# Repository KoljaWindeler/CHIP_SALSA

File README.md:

please go to 
http://koljawindeler.github.io/CHIP_SALSA

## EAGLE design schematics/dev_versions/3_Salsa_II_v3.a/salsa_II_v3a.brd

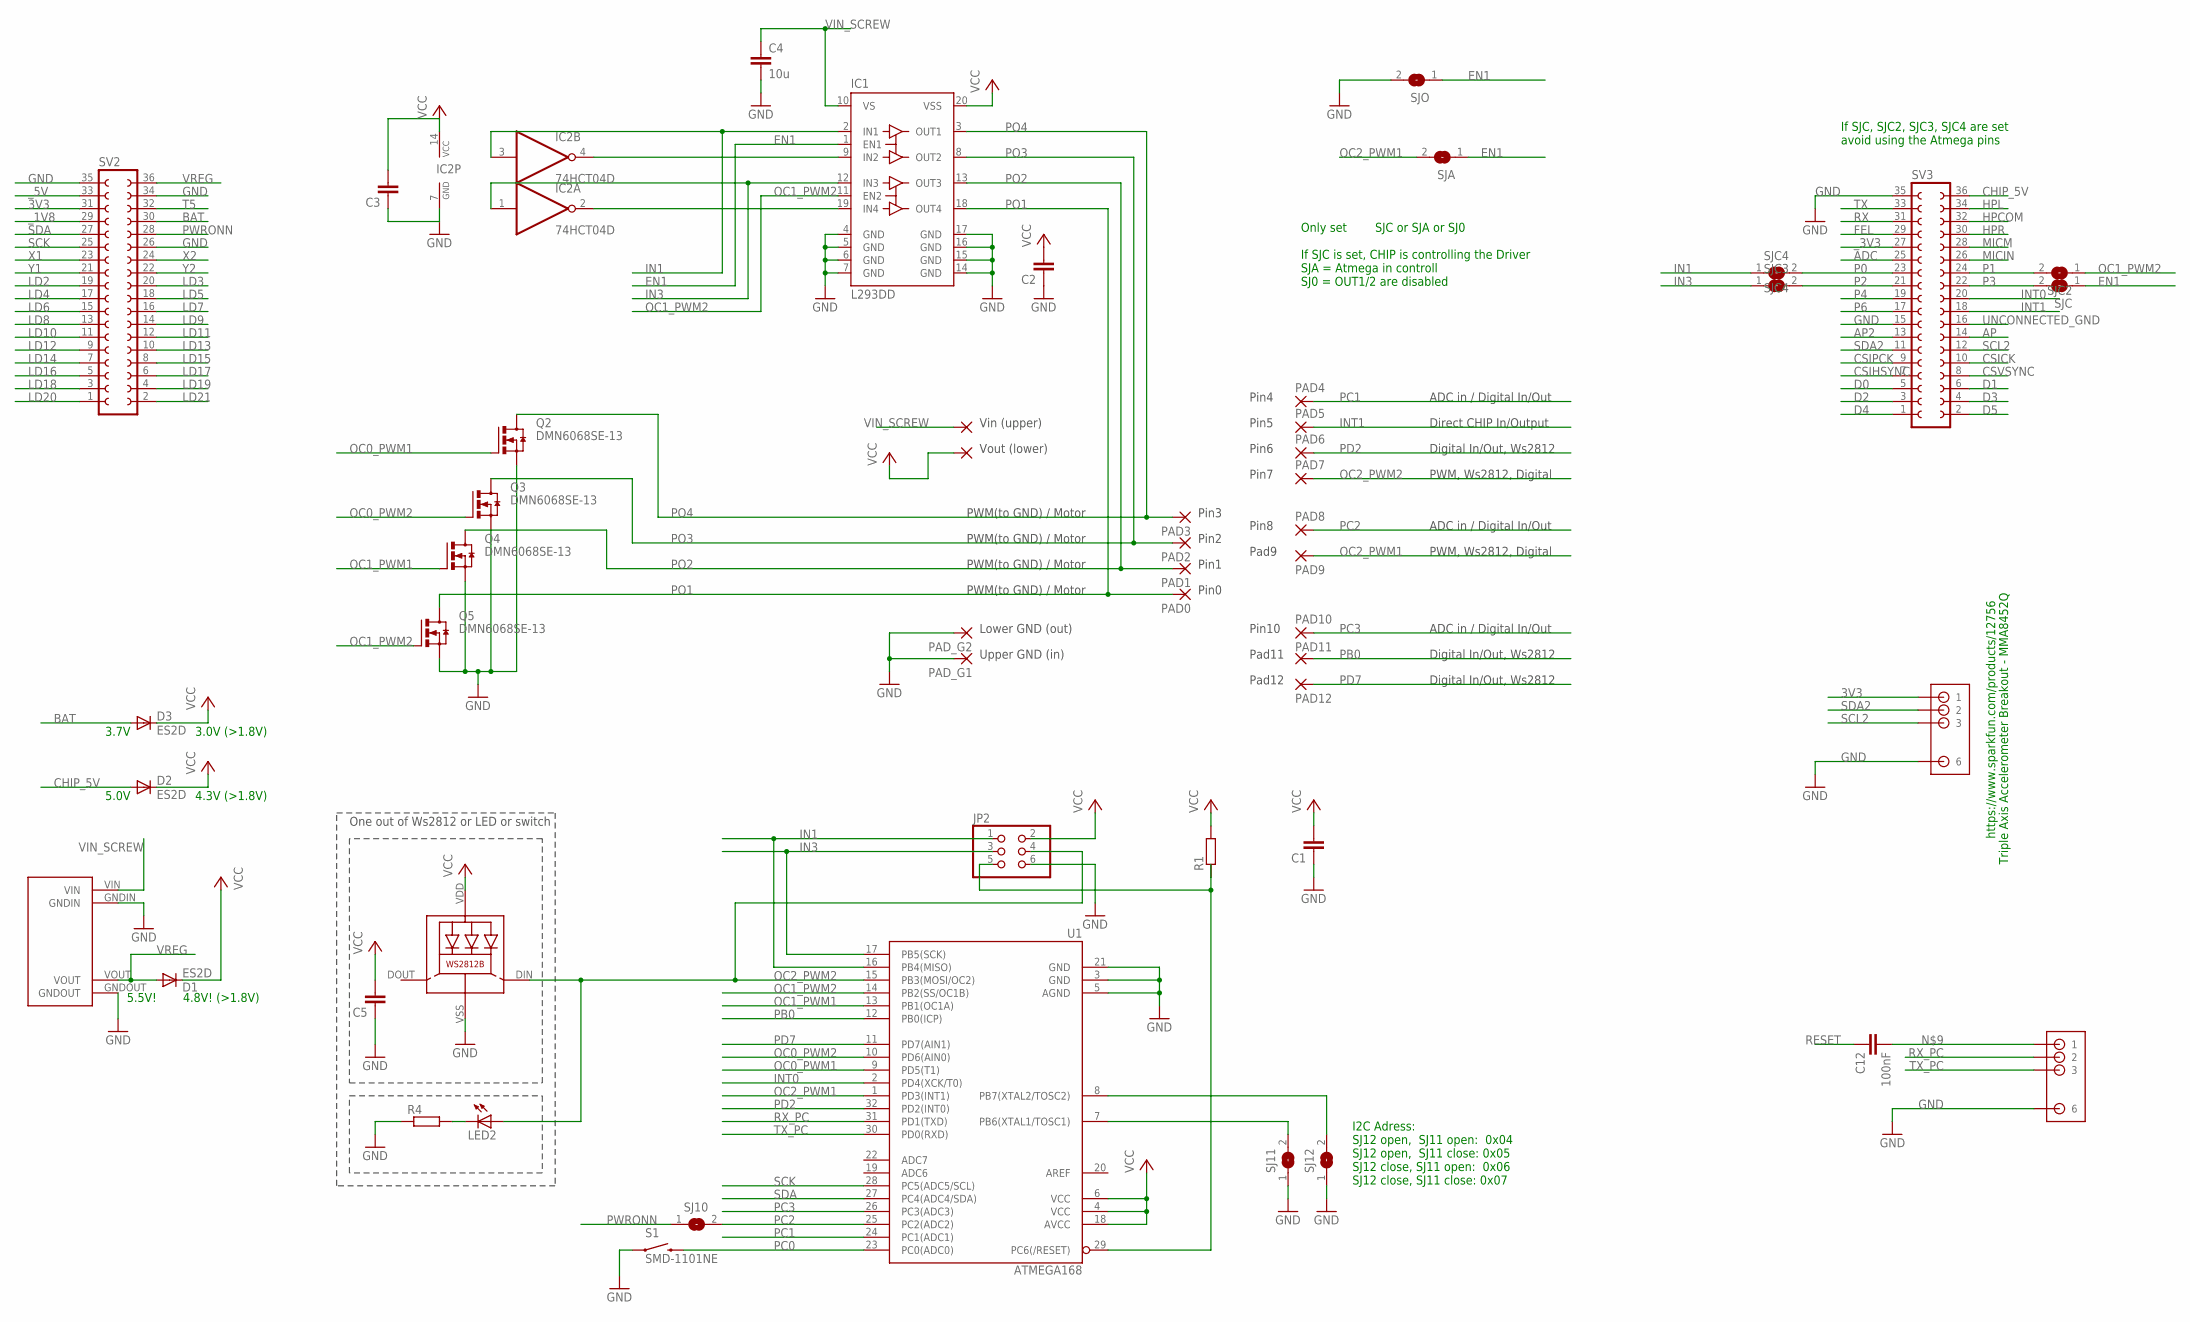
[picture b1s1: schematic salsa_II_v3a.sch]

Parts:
C1, C2, C3, C5: C-EUC0805; C0805
C4: 10u; C1210
C12: 100nF; C1206
D1, D2, D3: ES2D; SMB
IC1: L293DD; SO20
IC2: 74HCT04D; SO14
JP2: PINHD-2X3; 2X03
LED1: WS2812B
LED2: LEDCHIP-LED0805; CHIP-LED0805
PAD0, PAD1, PAD2, PAD3, PAD4, PAD5, PAD6, PAD7, PAD8, PAD10, PAD17: 3,17/1,3
PAD9, PAD12: SMD2; SMD1,27-2,54
PAD11: WIREPADSMD1,27-254; SMD1,27-2,54
PAD_G1, PAD_G2: 3,17/1,3
PAD_VIN: 3,17/1,3
Q2, Q3, Q4, Q5: DMN6068SE-13; SOT223
R1, R4: R-EU_M1206; M1206
S1: SMD-1101NE; TACTILE-SWITCH-1101NE
SJ10, SJ11, SJ12: SJ
SJA: SJ
SJC, SJC2, SJC3: SJ
SJC4: SJC4; SJ
SJO: SJ
SV2, SV3: FE18-2
U1: ATMEGA168; TQFP32-08
U$1: MP1584EN
U$3, U$4: 6_TO_4_HEADER

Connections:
3V3: SV2.31, U$4.1
ADC: SV3.25
AP: SV3.14
AP2: SV3.13
BAT: D3.A, SV2.30
CHIP_5V: D2.A, SV3.36
CSICK: SV3.10
CSIHSYNC: SV3.7
CSIPCK: SV3.9
CSVSYNC: SV3.8
D0: SV3.5
D1: SV3.6
D2: SV3.3
D3: SV3.4
D4: SV3.1
D5: SV3.2
EN1: IC1.1 (EN1), SJA.1, SJC.1, SJO.1
FEL: SV3.29
GND: C1.1, C2.1, C3.1, C4.2, C5.1, IC1.4 (GND), IC1.5 (GND), IC1.6 (GND), IC1.7 (GND), IC1.14 (GND), IC1.15 (GND), IC1.16 (GND), IC1.17 (GND), IC2.7 (GND), JP2.6, LED1.VSS (GND), PAD_G1.1, PAD_G2.1, Q2.3 (S), Q3.3 (S), Q4.3 (S), Q5.3 (S), R4.1, S1.P$1 (1), SJ11.1, SJ12.1, SJO.2, SV2.26, SV2.34, SV2.35, SV3.15, SV3.35, U1.3 (GND), U1.5 (AGND), U1.21 (GND), U$1.GNDIN, U$1.GNDOUT, U$3.6, U$4.6
HPCOM: SV3.32
HPL: SV3.34
HPR: SV3.30
IN1: IC1.2 (IN1), IC2.3 (I), JP2.1, SJC4.1, U1.16 (PB4(MISO))
IN3: IC1.12 (IN3), IC2.1 (I), JP2.3, SJC3.1, U1.17 (PB5(SCK))
INT0: SV3.20, U1.2 (PD4(XCK/T0))
INT1: PAD5.1, SV3.18
LD2: SV2.19
LD3: SV2.20
LD4: SV2.17
LD5: SV2.18
LD6: SV2.15
LD7: SV2.16
LD8: SV2.13
LD9: SV2.14
LD10: SV2.11
LD11: SV2.12
LD12: SV2.9
LD13: SV2.10
LD14: SV2.7
LD15: SV2.8
LD16: SV2.5
LD17: SV2.6
LD18: SV2.3
LD19: SV2.4
LD20: SV2.1
LD21: SV2.2
MICIN: SV3.26
MICM: SV3.28
unnamed: IC1.19 (IN4), IC2.2 (O)
unnamed: SJ11.2, U1.7 (PB6(XTAL1/TOSC1))
unnamed: SJ12.2, U1.8 (PB7(XTAL2/TOSC2))
unnamed: LED2.C, R4.2
unnamed: C12.2, U$3.1
unnamed: IC1.9 (IN2), IC2.4 (O)
OC0_PWM1: Q2.1 (G), U1.9 (PD5(T1))
OC0_PWM2: Q3.1 (G), U1.10 (PD6(AIN0))
OC1_PWM1: Q4.1 (G), U1.13 (PB1(OC1A))
OC1_PWM2: IC1.11 (EN2), Q5.1 (G), SJC2.1, U1.14 (PB2(SS/OC1B))
OC2_PWM1: PAD9.1, SJA.2, U1.1 (PD3(INT1))
OC2_PWM2: JP2.4, LED1.DIN (DI), LED2.A, PAD7.1, U1.15 (PB3(MOSI/OC2))
P0: SJC4.2, SV3.23
P1: SJC2.2, SV3.24
P2: SJC3.2, SV3.21
P3: SJC.2, SV3.22
P4: SV3.19
P6: SV3.17
PB0: PAD11.1, U1.12 (PB0(ICP))
PC0: S1.P$2 (2), U1.23 (PC0(ADC0))
PC1: PAD4.1, U1.24 (PC1(ADC1))
PC2: PAD8.1, SJ10.2, U1.25 (PC2(ADC2))
PC3: PAD10.1, U1.26 (PC3(ADC3))
PD2: PAD6.1, U1.32 (PD2(INT0))
PD7: PAD12.1, U1.11 (PD7(AIN1))
PO1: IC1.18 (OUT4), PAD0.1, Q5.2 (D), Q5.4 (D)
PO2: IC1.13 (OUT3), PAD1.1, Q4.2 (D), Q4.4 (D)
PO3: IC1.8 (OUT2), PAD2.1, Q3.2 (D), Q3.4 (D)
PO4: IC1.3 (OUT1), PAD3.1, Q2.2 (D), Q2.4 (D)
PWRONN: SJ10.1, SV2.28
RESET: C12.1, JP2.5, R1.1, U1.29 (PC6(/RESET))
RX: SV3.31
RX_PC: U1.31 (PD1(TXD)), U$3.2
SCK: SV2.25, U1.28 (PC5(ADC5/SCL))
SCL2: SV3.12, U$4.3
SDA: SV2.27, U1.27 (PC4(ADC4/SDA))
SDA2: SV3.11, U$4.2
T5: SV2.32
TX: SV3.33
TX_PC: U1.30 (PD0(RXD)), U$3.3
UNCONNECTED_GND: SV3.16
VCC: C1.2, C2.2, C3.2, C5.2, D1.C, D2.C, D3.C, IC1.20 (VSS), IC2.14 (VCC), JP2.2, LED1.VDD, PAD17.1, R1.2, U1.4 (VCC), U1.6 (VCC), U1.18 (AVCC)
VIN_SCREW: C4.1, IC1.10 (VS), PAD_VIN.1, U$1.VIN
VREG: D1.A, SV2.36, U$1.VOUT
X1: SV2.23
X2: SV2.24
Y1: SV2.21
Y2: SV2.22
_1V8: SV2.29
_3V3: SV3.27
_5V: SV2.33

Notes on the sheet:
https://www.sparkfun.com/products/12756
Triple Axis Accelerometer Breakout - MMA8452Q
Vin (upper)
Pin0
Pin1
Pin2
Pin3
Upper GND (in)
Lower GND (out)
Vout (lower)
Pin4
Pin5
Pad11
Pad12
Pad9
Pin6
Pin7
Pin8
Pin10
PWM(to GND) / Motor
ADC in / Digital In/Out
Direct CHIP In/Output
Digital In/Out, Ws2812
PWM, Ws2812, Digital
I2C Adress: SJ12 open, SJ11 open: 0x04 SJ12 open, SJ11 close: 0x05 SJ12 close, SJ11 open: 0x06 SJ12 close, SJ11 close: 0x07
Only set SJC or SJA or SJ0 If SJC is set, CHIP is controlling the Driver SJA = Atmega in controll SJ0 = OUT1/2 are disabled
If SJC, SJC2, SJC3, SJC4 are set avoid using the Atmega pins
One out of Ws2812 or LED or switch
5.5V!
4.8V! (>1.8V)
5.0V
4.3V (>1.8V)
3.0V (>1.8V)
3.7V

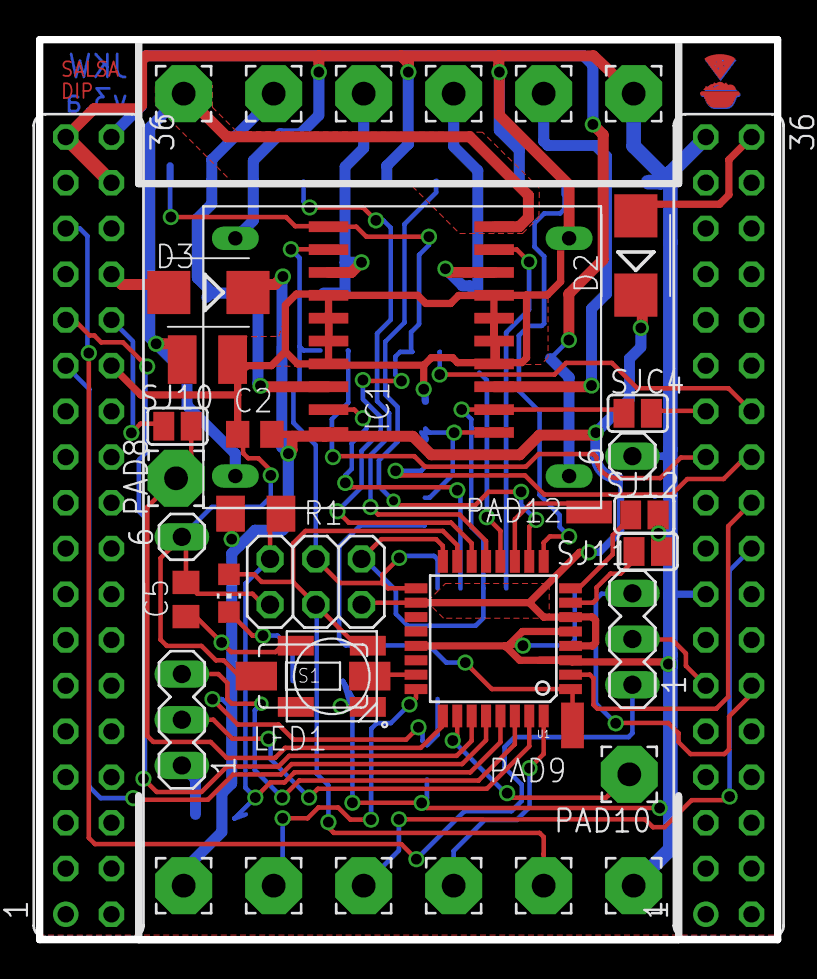
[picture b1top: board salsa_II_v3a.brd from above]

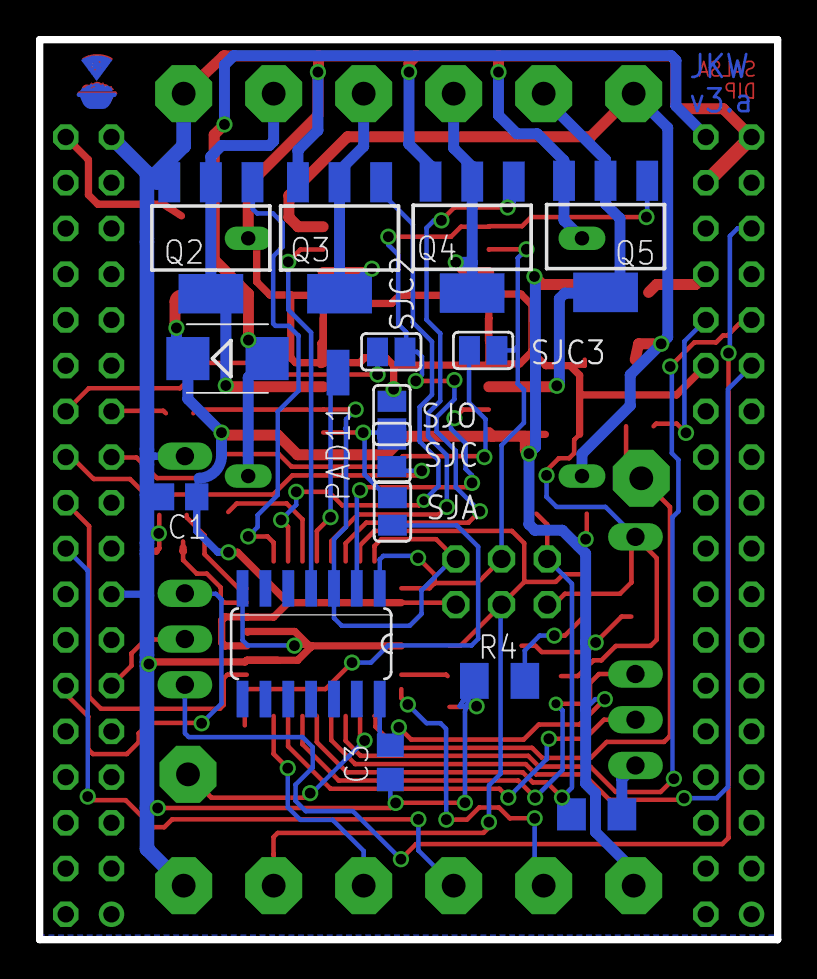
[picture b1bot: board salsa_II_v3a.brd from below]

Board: 2 copper layers, 41.0 x 50.0 mm, 55 parts (17 on the bottom side), 47 nets.

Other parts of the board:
U$2, U$5: LOGO

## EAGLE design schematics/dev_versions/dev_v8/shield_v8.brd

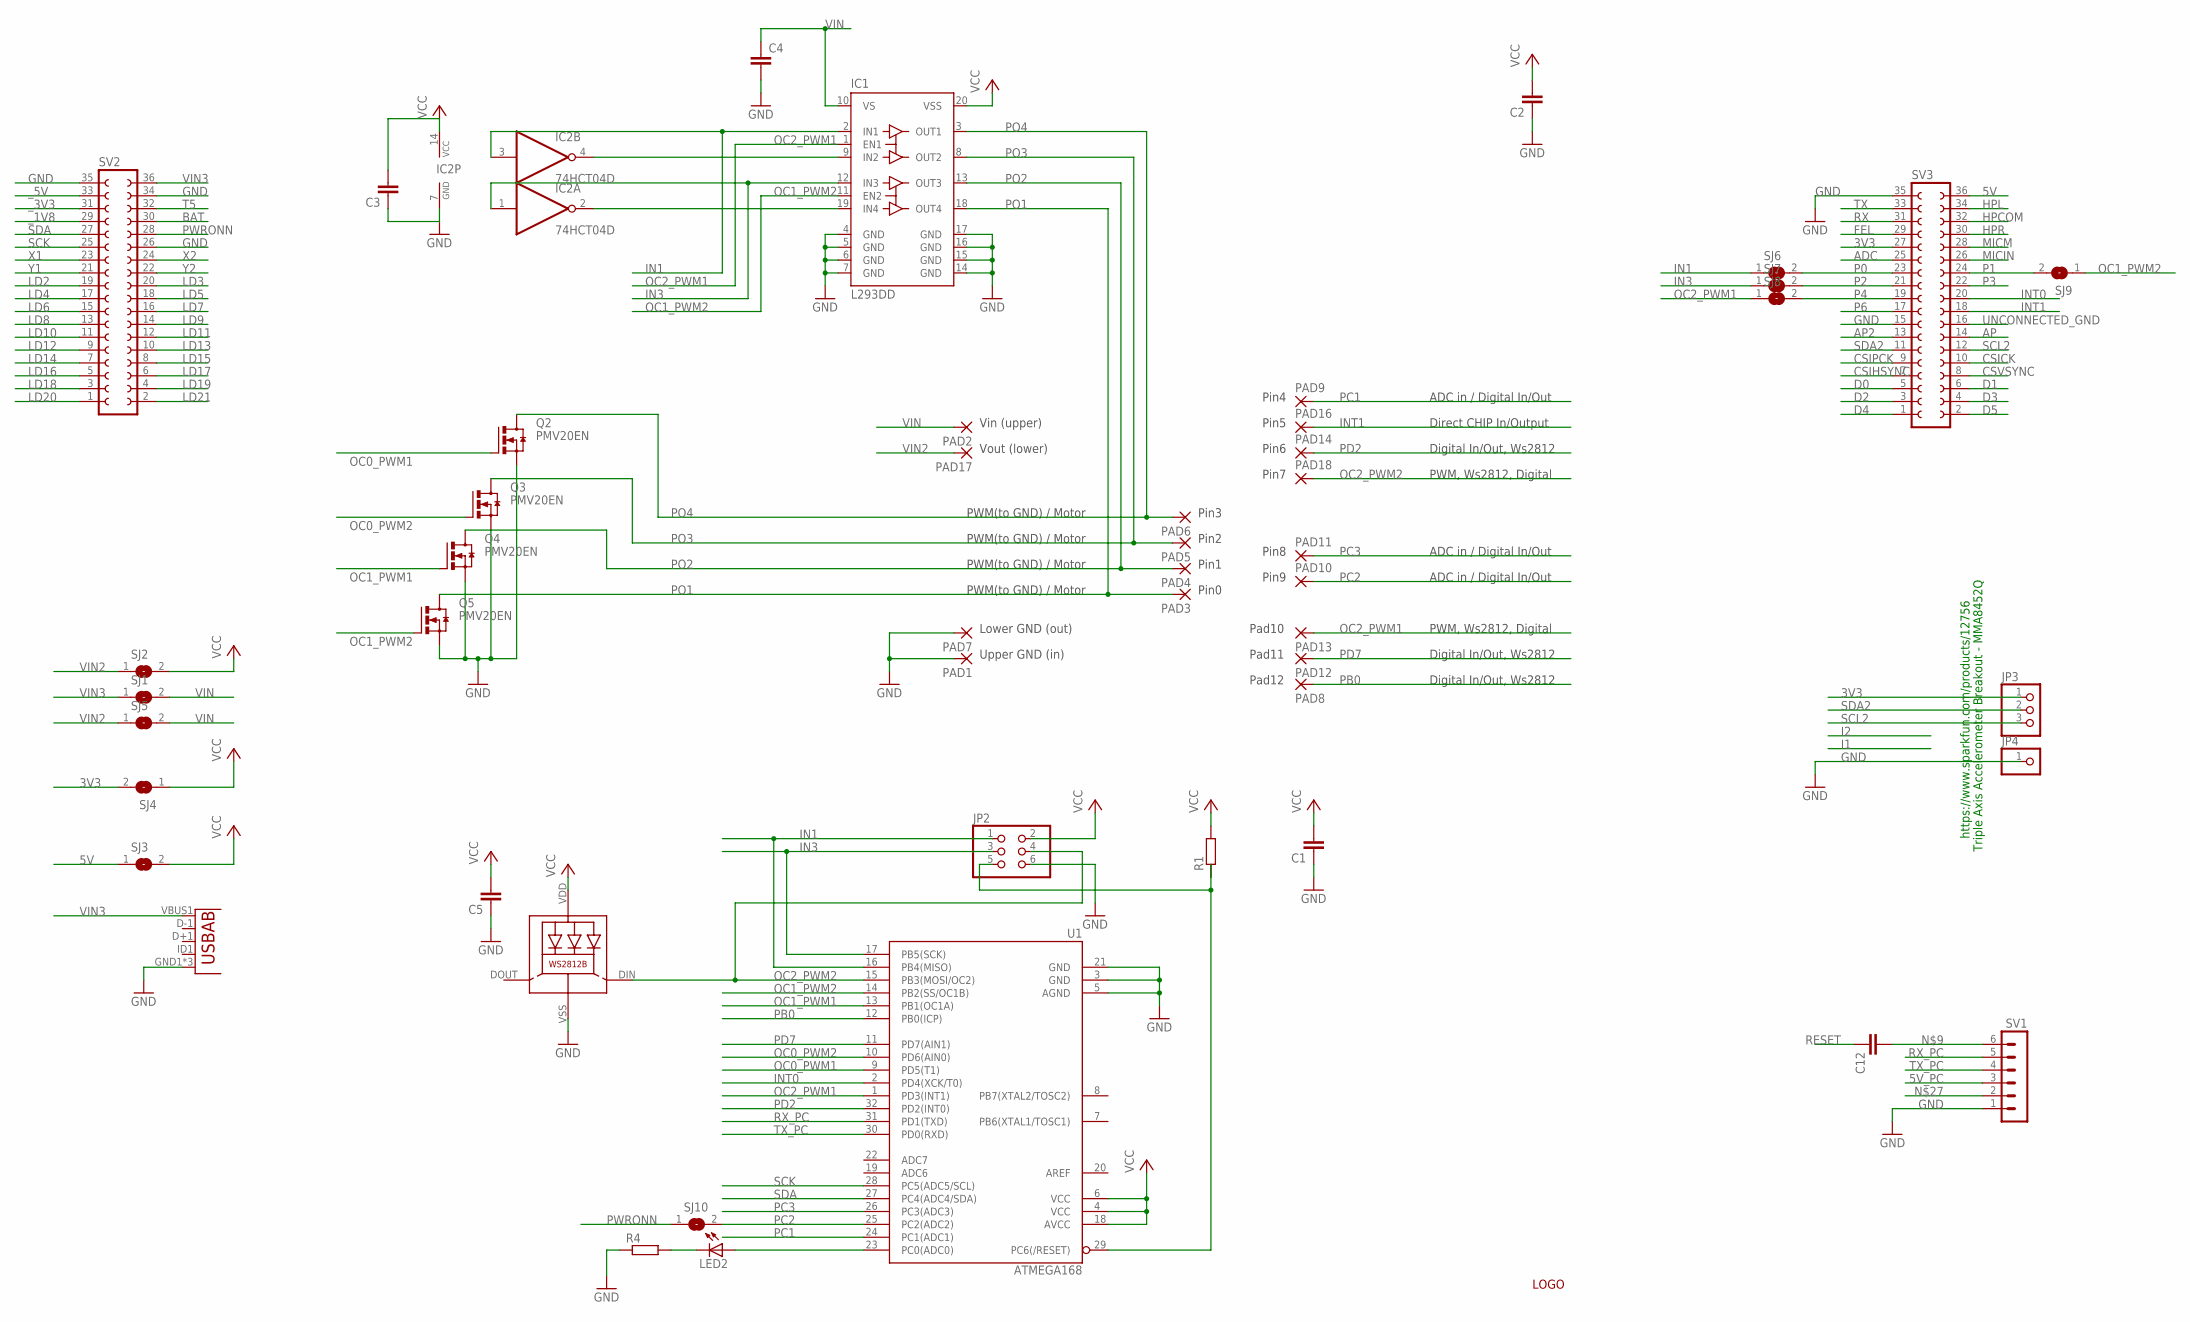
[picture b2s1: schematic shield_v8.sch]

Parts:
C1, C2, C3, C5: C-EUC0805; C0805
C4: C-EUC1210; C1210
C12: C-EUC1206; C1206
IC1: L293DD; SO20
IC2: 74HCT04D; SO14
JP2: PINHD-2X3; 2X03
JP3: PINHD-1X3; 1X03
JP4: PINHD-1X1; 1X01
LED1: WS2812B
LED2: LEDCHIP-LED0805; CHIP-LED0805
PAD1, PAD2, PAD3, PAD4, PAD5, PAD6, PAD7, PAD9, PAD10, PAD11, PAD14, PAD16, PAD17, PAD18: 3,17/1,3
PAD8: WIREPADSMD1,27-254; SMD1,27-2,54
PAD12, PAD13: SMD2; SMD1,27-2,54
Q2, Q3, Q4, Q5: PMV20EN; SOT223
R1, R4: R-EU_M1206; M1206
SJ1, SJ2, SJ3, SJ4, SJ5, SJ6, SJ7, SJ8, SJ9, SJ10: SJ
SV1: MA06-1
SV2, SV3: FE18-2
U1: ATMEGA168; TQFP32-08
U2: USB""; USB-MICRO-SMD
U$2: LOGO

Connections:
3V3: JP3.1, SJ4.2, SV3.27
5V: SJ3.1, SV3.36
5V_PC: SV1.3
ADC: SV3.25
AP: SV3.14
AP2: SV3.13
BAT: SV2.30
CSICK: SV3.10
CSIHSYNC: SV3.7
CSIPCK: SV3.9
CSVSYNC: SV3.8
D0: SV3.5
D1: SV3.6
D2: SV3.3
D3: SV3.4
D4: SV3.1
D5: SV3.2
FEL: SV3.29
GND: C1.1, C2.1, C3.1, C4.2, C5.1, IC1.4 (GND), IC1.5 (GND), IC1.6 (GND), IC1.7 (GND), IC1.14 (GND), IC1.15 (GND), IC1.16 (GND), IC1.17 (GND), IC2.7 (GND), JP2.6, JP4.1, LED1.VSS (GND), PAD1.1, PAD7.1, Q2.3 (S), Q3.3 (S), Q4.3 (S), Q5.3 (S), R4.1, SV1.1, SV2.26, SV2.34, SV2.35, SV3.15, SV3.35, U1.3 (GND), U1.5 (AGND), U1.21 (GND), U2.GND1 (GND), U2.GND2 (GND), U2.GND3 (GND)
HPCOM: SV3.32
HPL: SV3.34
HPR: SV3.30
IN1: IC1.2 (IN1), IC2.3 (I), JP2.1, SJ6.1, U1.16 (PB4(MISO))
IN3: IC1.12 (IN3), IC2.1 (I), JP2.3, SJ7.1, U1.17 (PB5(SCK))
INT0: SV3.20, U1.2 (PD4(XCK/T0))
INT1: PAD16.1, SV3.18
LD2: SV2.19
LD3: SV2.20
LD4: SV2.17
LD5: SV2.18
LD6: SV2.15
LD7: SV2.16
LD8: SV2.13
LD9: SV2.14
LD10: SV2.11
LD11: SV2.12
LD12: SV2.9
LD13: SV2.10
LD14: SV2.7
LD15: SV2.8
LD16: SV2.5
LD17: SV2.6
LD18: SV2.3
LD19: SV2.4
LD20: SV2.1
LD21: SV2.2
MICIN: SV3.26
MICM: SV3.28
unnamed: IC1.19 (IN4), IC2.2 (O)
unnamed: C12.2, SV1.6
unnamed: IC1.9 (IN2), IC2.4 (O)
unnamed: LED2.C, R4.2
unnamed: LED2.A, U1.23 (PC0(ADC0))
OC0_PWM1: Q2.1 (G), U1.9 (PD5(T1))
OC0_PWM2: Q3.1 (G), U1.10 (PD6(AIN0))
OC1_PWM1: Q4.1 (G), U1.13 (PB1(OC1A))
OC1_PWM2: IC1.11 (EN2), Q5.1 (G), SJ9.1, U1.14 (PB2(SS/OC1B))
OC2_PWM1: IC1.1 (EN1), PAD13.1, SJ8.1, U1.1 (PD3(INT1))
OC2_PWM2: JP2.4, LED1.DIN (DI), PAD18.1, U1.15 (PB3(MOSI/OC2))
P0: SJ6.2, SV3.23
P1: SJ9.2, SV3.24
P2: SJ7.2, SV3.21
P3: SV3.22
P4: SJ8.2, SV3.19
P6: SV3.17
PB0: PAD8.1, U1.12 (PB0(ICP))
PC1: PAD9.1, U1.24 (PC1(ADC1))
PC2: PAD10.1, SJ10.2, U1.25 (PC2(ADC2))
PC3: PAD11.1, U1.26 (PC3(ADC3))
PD2: PAD14.1, U1.32 (PD2(INT0))
PD7: PAD12.1, U1.11 (PD7(AIN1))
PO1: IC1.18 (OUT4), PAD3.1, Q5.2 (D), Q5.4 (D)
PO2: IC1.13 (OUT3), PAD4.1, Q4.2 (D), Q4.4 (D)
PO3: IC1.8 (OUT2), PAD5.1, Q3.2 (D), Q3.4 (D)
PO4: IC1.3 (OUT1), PAD6.1, Q2.2 (D), Q2.4 (D)
PWRONN: SJ10.1, SV2.28
RESET: C12.1, JP2.5, R1.1, U1.29 (PC6(/RESET))
RX: SV3.31
RX_PC: SV1.5, U1.31 (PD1(TXD))
SCK: SV2.25, U1.28 (PC5(ADC5/SCL))
SCL2: JP3.3, SV3.12
SDA: SV2.27, U1.27 (PC4(ADC4/SDA))
SDA2: JP3.2, SV3.11
T5: SV2.32
TX: SV3.33
TX_PC: SV1.4, U1.30 (PD0(RXD))
UNCONNECTED_GND: SV3.16
VCC: C1.2, C2.2, C3.2, C5.2, IC1.20 (VSS), IC2.14 (VCC), JP2.2, LED1.VDD, R1.2, SJ2.2, SJ3.2, SJ4.1, U1.4 (VCC), U1.6 (VCC), U1.18 (AVCC)
VIN: C4.1, IC1.10 (VS), PAD2.1, SJ1.2, SJ5.2
VIN2: PAD17.1, SJ2.1, SJ5.1
VIN3: SJ1.1, SV2.36, U2.VBUS1 (VBUS)
X1: SV2.23
X2: SV2.24
Y1: SV2.21
Y2: SV2.22
_1V8: SV2.29
_3V3: SV2.31
_5V: SV2.33

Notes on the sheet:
https://www.sparkfun.com/products/12756
Triple Axis Accelerometer Breakout - MMA8452Q
Vin (upper)
Pin0
Pin1
Pin2
Pin3
Upper GND (in)
Lower GND (out)
Vout (lower)
Pin4
Pin5
Pad12
Pad11
Pad10
Pin6
Pin7
Pin9
Pin8
PWM(to GND) / Motor
ADC in / Digital In/Out
Direct CHIP In/Output
Digital In/Out, Ws2812
PWM, Ws2812, Digital

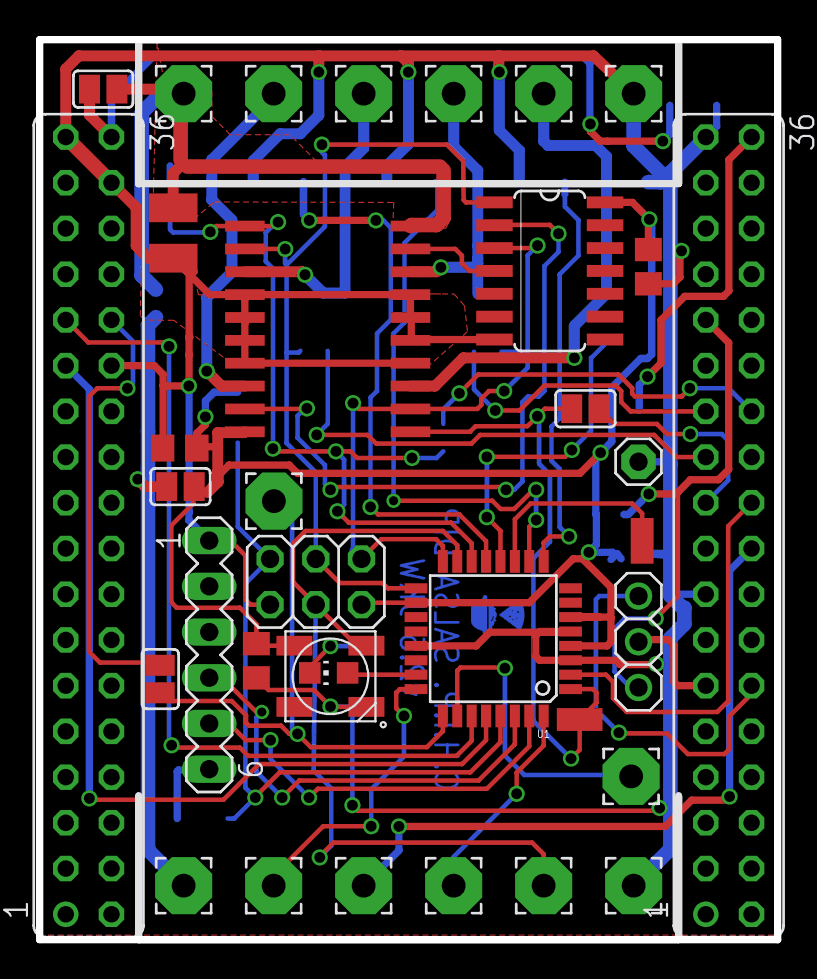
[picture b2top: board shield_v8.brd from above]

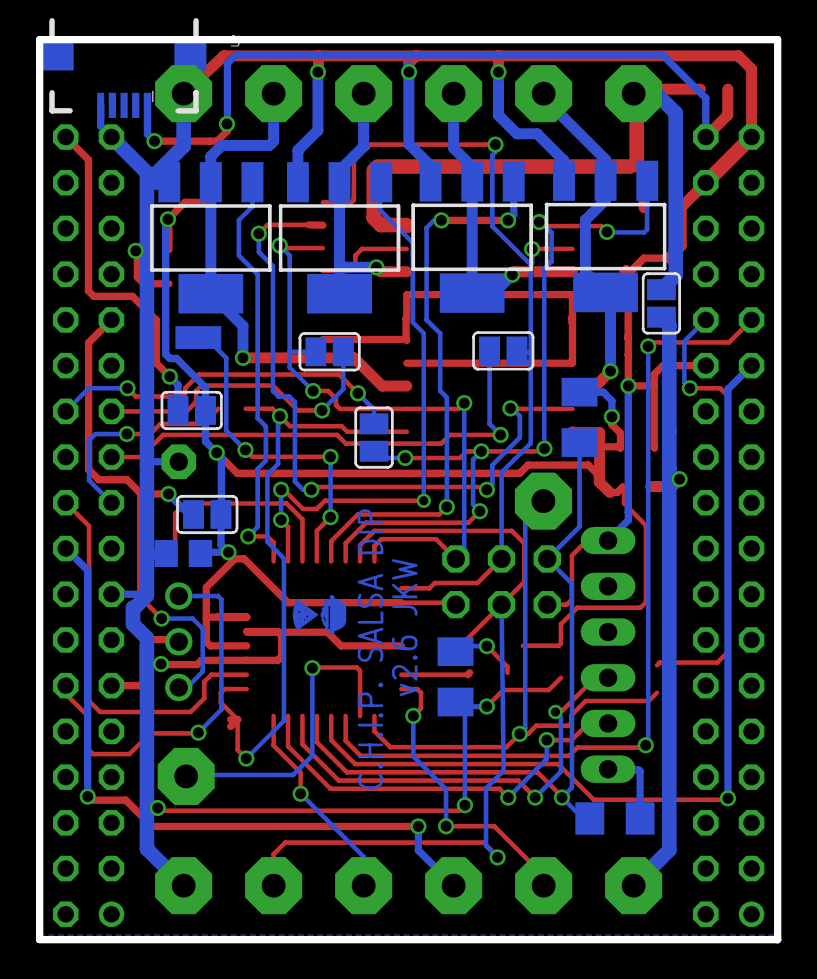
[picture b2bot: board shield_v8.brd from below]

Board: 2 copper layers, 41.0 x 50.0 mm, 52 parts (16 on the bottom side), 44 nets.

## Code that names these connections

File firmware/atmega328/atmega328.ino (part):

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
//========================= i2c config and init? =========================//
void setup(){
	// Activate Pin PB6 and PB7 input pull up and read i2c address adder value
	DDRB &= ~((1 << 6) & (1 << 7));
	PORTB |= (1 << 6) | (1 << 7); 
	delay(10); // 10ms to pull the pin up
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	// prepare
	//set( 		ana,  digi,  pwm,   ws,   Arduino_pin);
	// screw outputs
	m_pins[0].set( false, true,  true,  true,  10); 	// PB2, P0 PWM or left motor driver (P0/1) En signal
	m_pins[1].set( false, true,  true,  true,  9); 		// PB1, P1 PWM
	m_pins[2].set( false, true,  true,  true,  6); 		// PD6, P2 PWM
	m_pins[3].set( false, true,  true,  true,  5); 		// PD5, P3 PWM
	m_pins[4].set( true,  true,  false, false, 15); 	// PC1, P4 analog input
	m_pins[5].set( false, false, false, false, 0xff); 	//      P5 direct to CHIP P7 pin
	m_pins[6].set( false, true,  false, true,  2); 		// PD2, P6 digital and ws2812 pin
	m_pins[7].set( false, true,  true,  true,  11); 	// PB3, P7 and to onboard ws2812 and to general LED

	// some pins spread over the board
	m_pins[8].set( true,  true,  false, false, 16); 	// PC2, PAD8 and jumper to powerdown
	m_pins[9].set( false, true,  true,  true,  3); 		// PD3, PAD9 and right motor driver (P2/3) En signal
	m_pins[10].set(true,  true,  false, false, 17); 	// PC3, PAD10
	m_pins[11].set(false, true,  false, true,  8); 		// PB0, PAD11
	m_pins[12].set(false, true,  false, true,  7); 		// PD7, PAD12

	// internal pins
	m_pins[13].set(false, true,  false, false, 12); 	// PB4, internal pin to motor driver, direction pins, right side (P2/3), function limited
	m_pins[14].set(false, true,  false, false, 13); 	// PB5, internal pin to motor driver,  direction pins, left side (P0/1), function limited
	m_pins[15].set(false, true,  false, false, 4);  	// PD4, internal pin to CHIP, e.g. interrupts
	m_pins[16].set(false, true,  false, false, 14); 	// PC0, internal pin, to optional switch

	
	Wire.begin(I2C_ADDRESS+i2c_adder);                // join i2c bus with address #4,5,6 or 7
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
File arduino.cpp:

//#include </home/kolja/projects/CHIP_pwm_shield/atmega328/WS2812.h>	// thanks Matthias Riegler!
#include <WS2812.h>	// thanks Matthias Riegler!
#include <Wire.h>
// -------------------------------------------------------------------------------------------------------------------------------------------------------------//
// config pin 5 as  pwm 			START_BYTE, 	CMD_CONFIG, 5, MODE_PWM
// set all 50%					START_BYTE, 	CMD_SET, 5, 128
// ---------------------------------------------------------------------------------------------------------------
// config pin 9 as  5 x same ws2812		START_BYTE, 	CMD_CONFIG, 9, MODE_SINGLE_COLOR_WS2812, 5
// set all red 					START_BYTE, 	CMD_SET, 9, 0xff, 0x00,0x00
// set all green				START_BYTE, 	CMD_SET, 9, 0x00, 0xff,0x00
// ---------------------------------------------------------------------------------------------------------------
// config pin 10 as  3 x unique ws2812 		START_BYTE, 	CMD_CONFIG, 10, MODE_MULTI_COLOR_WS2812, 3
// set all 1xr,1xg,1xb 				START_BYTE, 	CMD_SET, 10, 	0xff, 0x00,0x00, 	0x00, 0xff,0x00, 	0x00, 0x00,0xff
// ---------------------------------------------------------------------------------------------------------------
// restart, erase config			START_BYTE, 	CMD_RESET
// -------------------------------------------------------------------------------------------------------------------------------------------------------------//

#define START_BYTE		0xCE
#define CMD_SET 		0xF0
#define CMD_CONFIG		0xF1
#define CMD_READ		0xF2
#define CMD_RESET		0xF3

#define MODE_PWM			0x01
#define MODE_INPUT			0x02
#define MODE_SINGLE_COLOR_WS2812	0x03
#define MODE_MULTI_COLOR_WS2812		0x04
#define MAX_MODE			MODE_MULTI_COLOR_WS2812

#define ST_WAIT 			0xFF
#define ST_CMD 				0x00
#define ST_CONFIG_CHANNEL		0x01
#define ST_CONFIG_MODE 			0x02
#define ST_SET_CHANNEL			0x03
#define ST_SET_SINGLE_VALUE 		0x04
#define ST_SET_VALUE_R 			0x05
#define ST_SET_VALUE_G 			0x06
#define ST_SET_VALUE_B			0x07
#define ST_WS2812_NUM			0x08

#define TRANSFER_TIMEOUT 200
#define I2C_ADDRESS	0x04

uint8_t  m_state=ST_WAIT;
uint8_t	 m_channel=0;
uint8_t	 m_value_r=0;
uint8_t	 m_value_g=0;
uint8_t	 m_value_b=0;
uint8_t	 m_value=0;
uint8_t	 m_current_led=0;
uint32_t m_lasttransfer=0;
uint8_t m_modes[5+4+4]; // 5+4+4 channels
uint8_t m_ws_count[4]; //  only lower 4 channels
WS2812* m_ws2812[4]; //  only lower 4 channels
cRGB value;


// i2c config and init
void setup(){
	Wire.begin(I2C_ADDRESS);                // join i2c bus with address #4
	Wire.onReceive(receiveEvent); // register event
	for(int i=0; i<13; i++){
		m_modes[i]=0xff; // invalid
	}
	for(int i=0; i<4; i++){
		m_ws_count[i]=0;
	}
	//Serial.begin(19200);
	//Serial.println("Hi");
}

// timeout
void loop(){
	delay(TRANSFER_TIMEOUT);
	if(millis()-m_lasttransfer>TRANSFER_TIMEOUT){
		m_state=ST_WAIT;
	}
}

//declare reset function @ address 0
void(* resetFunc) (void) = 0; 

int shield_to_arduino_pin(uint8_t shield_pin){
	// channel row 1, left-to-right:	|| 	11(PB3), 	10(PB2),	9(PB1), 	6(PD6), 	5(PD5)	||
	// channel row 2, left-to-right:	||	 -(ADC7), 	A1/15(PC1), 	A2/16(PC2), 	A3/17(PC3),	XXX	||
	// channel row 3, left-to-right: 	||	0(PD0), 	1(PD1), 	2(PD2), 	3(PD3),		XXX	|| only these are used for up to 4 parallel ws2812 channels
	
	if(shield_pin==0)	{	return	11;	}	// upper left
	else if(shield_pin==1)	{	return	10;	}
	else if(shield_pin==2)	{	return	9;	}
	else if(shield_pin==3)	{	return	6;	}
	else if(shield_pin==4)	{	return	5;	} // upper right
	
	//else if(shield_pin==5){	return	0;	} // middle left
	else if(shield_pin==6)	{	return	15;	}
	else if(shield_pin==7)	{	return	16;	}
	else if(shield_pin==8)	{	return	17;	} // middle right
	
	else if(shield_pin==9)	{	return	0;	} // lower left
	else if(shield_pin==10)	{	return	1;	}
	else if(shield_pin==11)	{	return	2;	}
	else if(shield_pin==12)	{	return	3;	} // lower right
	
	return -1; // hmm
}

// setup - on-the-fly
void config_pin(uint8_t pin){
	if(m_modes[pin]==MODE_PWM){
		pinMode(pin,OUTPUT);
	} else if(m_modes[pin]==MODE_INPUT){
		if(pin>=6 && pin<=8){
			pinMode(pin,INPUT);
		}
	} else if(m_modes[pin]==MODE_SINGLE_COLOR_WS2812 || m_modes[pin]==MODE_MULTI_COLOR_WS2812){
		if(pin>=9 && pin<=11){
			WS2812 *ws2812 = new WS2812(m_ws_count[pin-9]);
			ws2812->setOutput(shield_to_arduino_pin(pin)); 
			m_ws2812[pin-9]=ws2812; // save pointer
		}
	}
}

// control the led
void set_value(){
	// pwm
	if(m_modes[m_channel]==MODE_PWM){ // output digital
		digitalWrite(m_channel,m_value);
	}	// pwm end 
	
	// ws2812
	else if(m_modes[m_channel]==MODE_SINGLE_COLOR_WS2812 || m_modes[m_channel]==MODE_MULTI_COLOR_WS2812){ // output pixel
		// get values
		value.r = m_value_r; 
		value.g = m_value_g; 
		value.b = m_value_b; // RGB Value -> Blue
		// 
		if(m_modes[m_channel]==MODE_SINGLE_COLOR_WS2812){
			for(int i=0; i<m_ws_count[m_channel-9]; i++){
				m_ws2812[m_channel-9]->set_crgb_at(i, value); // Set value at all LEDs
			}
			m_ws2812[m_channel-9]->sync(); // Sends the value to the LED
		} else if(m_modes[m_channel]==MODE_MULTI_COLOR_WS2812){ 
			m_ws2812[m_channel-9]->set_crgb_at(m_current_led, value); // Set value at LED found at RUNNING INDEX
			m_current_led++;
			if(m_current_led>=m_ws_count[m_channel-9]){
				m_ws2812[m_channel-9]->sync(); // Sends the value to the LED only when all value are known
			}
		}
	}	// ws 2812 end
}


// function that executes whenever data is received from master
// this function is registered as an event, see setup()
void receiveEvent(int howMany){
	while(Wire.available()){ // loop through all but the last
		m_lasttransfer=millis();
		unsigned char c = Wire.read(); // receive byte as a character
		//Serial.println(c,DEC);      // print the character
		
		//############# HEADER ###############
		if(m_state==ST_CMD){
			if(c == CMD_SET){
				m_state = ST_SET_CHANNEL;
			} else if(c == CMD_CONFIG) {
				m_state = ST_CONFIG_CHANNEL;
			} else if(c == CMD_RESET) {
				resetFunc();  //call reset
			}
		} else if(m_state==ST_SET_CHANNEL || m_state==ST_CONFIG_CHANNEL ){
			m_channel = c;
			if(m_state==ST_CONFIG_CHANNEL) {			
				m_state=ST_CONFIG_MODE;	
			} else {
				if(m_modes[m_channel]==MODE_PWM){	
					m_state=ST_SET_SINGLE_VALUE;	
				} else if(m_modes[m_channel]==MODE_SINGLE_COLOR_WS2812 || m_modes[m_channel]==MODE_MULTI_COLOR_WS2812){	
					m_state=ST_SET_VALUE_R;
				}
			}
		} 
		//############# HEADER ###############
		//############# setup ###############
		else if(m_state==ST_CONFIG_MODE){
			if(c<=MAX_MODE){
				m_modes[m_channel]=c;
				if(c==MODE_SINGLE_COLOR_WS2812 || c==MODE_MULTI_COLOR_WS2812){
					m_state=ST_WS2812_NUM;
				} else {
					m_state=ST_WAIT;
					config_pin(m_channel);
				}
			} else {
				m_state=ST_WAIT;
			}
		} else if(m_state==ST_WS2812_NUM){
			m_ws_count[m_channel]=c;
			m_state=ST_WAIT;
			config_pin(m_channel);
		}
		//############# setup ###############	
		//############ set value #############
		else if(m_state==ST_SET_SINGLE_VALUE){		// pwm
			m_value=c;
			m_state=ST_WAIT;
			set_value();
		} else if(m_state==ST_SET_VALUE_R){	// MODE_SINGLE_COLOR_WS2812 or MODE_MULTI_COLOR_WS2812
			m_value_r=c;
			m_state=ST_SET_VALUE_G;
		} else if(m_state==ST_SET_VALUE_G){
			m_value_g=c;
			m_state=ST_SET_VALUE_B;
		} else if(m_state==ST_SET_VALUE_B){
			m_value_b=c;
			set_value();	
			if(m_modes[m_channel]==MODE_MULTI_COLOR_WS2812){ 	// maybe we have to go back to red
				if(m_current_led>=m_ws_count[m_channel-9]){ 					// set_value sets m_current_led++
					m_state=ST_WAIT; // done
				} else {
					m_state=ST_SET_VALUE_R; // resume
				}
			} else { // mode ws2812 .. single color, done!
				m_state=ST_WAIT;
			}
		} 
		//############ set value #############
		//############ start #############
		else if(c==START_BYTE){
			m_state=ST_CMD;
		}
		//############ start #############
	}
}

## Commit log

2016-01-02 init
2016-01-03 added 3.3/5V, a chargin pin and fixed chip layout
2016-01-03 added firmware v0.1
2016-01-14 added ws2812
2016-01-14 added all leds one color
2016-01-14 removed pin 12 from ws2812, N-Mosfet will avoid Ws2812 cmds
2016-01-15 multi ws2812 support
2016-01-15 rem dup
2016-01-15 resort
2016-01-19 added reset cap
2016-01-19 added bootloader
2016-01-19 added comments for setup and testcode
2016-01-25 added examples
2016-01-25 added i2c lib install script
2016-01-25 added more examples (partly untested)
2016-01-25 added support for reading commands (untested)
2016-01-25 removed : from filename
2016-01-25 added python class and some testfiles
2016-01-25 Added jumper to drive atmega via Vin or CHIP 5V or CHIP3.3V
2016-01-26 first round of fixes
2016-01-26 firmware fixes
2016-01-26 added comment, and response function
2016-01-26 added todos as reminder for new board
2016-01-26 moved working examples
2016-01-26 fixed poor man rainbow to full 3*255 colors
2016-01-27 improved lib, added tested scripts
2016-01-27 added digital write
2016-01-27 added the motor driver and inverter to the pwm shield
2016-01-28 Added Pinout and jumper description
2016-01-29 added version 2.2 with solder jumper from CHIP GPIO to Motor driver
2016-01-29 updated routing
2016-01-31 copied digital pin settings to arduino file
2016-01-31 rerouting to fix osh DRU issues
2016-01-31 cleaned schematics
2016-01-31 added order note
2016-02-01 added salsa v6 with 10mil wire
2016-02-03 add read libs
2016-02-03 added reading
2016-02-04 added logo
2016-02-05 moved motor driver lower
2016-02-08 added micro usb connector
2016-02-09 added adress selector
2016-02-09 added v2.7 pinout
2016-02-09 corrected for pinout v2.7
2016-02-10 added 14/15 as pins
2016-02-10 updates examples
2016-02-10 added bash commands
2016-02-11 not working but shorter
2016-02-11 added dimming
2016-02-11 added gerber files for ordered version
2016-02-11 newer shorter nicer version running
2016-02-11 example for dimming
2016-02-11 debug for the dimming cmd added
2016-02-18 added pinout for LED and motor shield, seeedstudio version
2016-02-24 renamed versions
2016-02-24 removed copies
2016-02-24 added firmware burn command
2016-02-24 added step down
2016-02-24 Added power supply lib
2016-02-26 renamed examples
2016-02-26 mv files
2016-02-26 added testsoftware
2016-03-02 added salsa II board, ordered at seeedstudio today
2016-03-02 cleaned version structure for forum
2016-03-02 added solder jumper layout for preSalsa board
2016-03-02 added motor solder jumper guide
2016-03-02 joined documentation to avoid confusion .. not done
2016-03-03 added assembled board
2016-03-03 moved version 3 to dev as 3b was ordered
2016-03-03 fixed font
2016-03-03 moved fonts to silk
2016-03-03 added pictues
2016-03-03 added pdf version for NTC
2016-03-04 Added pin description and activates more capabilities
2016-03-04 Added motor pins to pinout slide
2016-03-06 added pwm freq setup
2016-03-06 eased freq selection
2016-03-06 freq fixe
2016-03-06 made the freq controll easier
2016-03-06 removed debug msg
2016-03-07 added comments to pins
2016-03-07 added EL ER DL DR for motor pinout
2016-03-08 added target price
2016-03-10 all-in-one demo
2016-03-10 added on board led to hdd
2016-03-10 add full install script
2016-03-10 fixed some settings
2016-03-16 updated libs
2016-03-23 updated menu
2016-03-23 updated hdd
2016-03-26 Create gh-pages branch via GitHub
2016-03-26 updated ignore
2016-03-26 improved text
2016-03-27 fixed link
2016-03-27 added missing img
2016-03-27 fixed html
2016-03-27 fordsfords fix
2016-03-27 typo
2016-03-30 added toggle after sleep
2016-03-30 added connection to power pin
2016-04-01 fixe intent
2016-04-01 fixed time
2016-04-01 double push
2016-04-01 added power safer chart
2016-04-04 added dimm function
2016-04-16 added setup images
2016-04-16 added sunrise
2016-04-16 added reboot video and arduino instructions
2016-04-16 added info about powersupply
2016-04-17 added schematic for mosfet
2016-04-18 added avrdude hack
2016-04-18 added gpio avrdude text
2016-04-28 pdfs
2016-07-21 added onion2 to hdd, moved libs, dru, cam to common
2016-07-30 addedoverlay
2016-08-16 added assign function to check for old ws2812 object and free it
2016-08-20 mv doc to common dir
2017-01-22 added driver test

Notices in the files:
parts and their libraries:
SparkFun-DigitalIC: Licensing: Creative Commons ShareAlike 4.0 International - https://creativecommons.org/licenses/by-sa/4.0
